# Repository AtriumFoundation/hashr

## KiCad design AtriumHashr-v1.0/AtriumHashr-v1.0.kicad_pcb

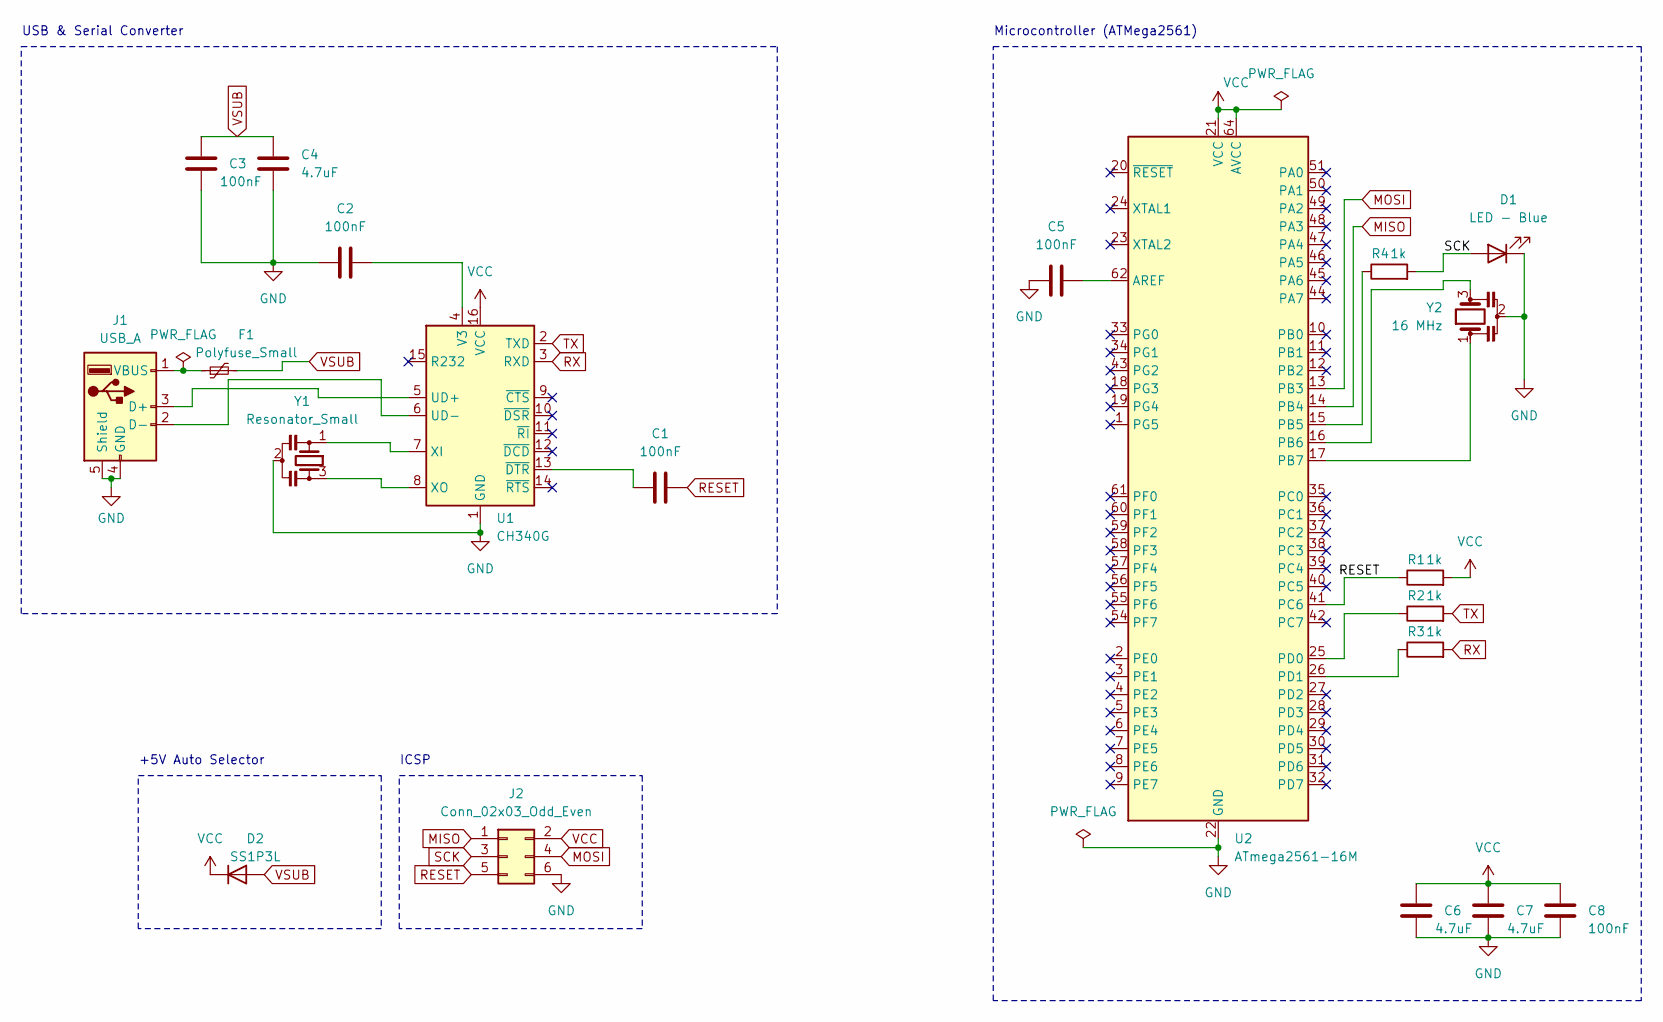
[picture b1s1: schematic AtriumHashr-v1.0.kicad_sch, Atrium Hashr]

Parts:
C1, C2, C3, C5, C8: 100nF; C_0402_1005Metric
C4, C6, C7: 4.7uF; C_0402_1005Metric
D1: LED - Blue; LED_0402_1005Metric
D2: SS1P3L; D_0402_1005Metric
F1: Polyfuse_Small; Fuse_0402_1005Metric
J1: USB_A; USB_A_CNCTech_1001-011-01101_Horizontal
J2: Conn_02x03_Odd_Even; PinHeader_2x03_P2.54mm_Vertical
R1, R2, R3, R4: 1k; R_0402_1005Metric
U1: CH340G; SOIC-16_3.9x9.9mm_P1.27mm
U2: ATmega2561-16M; QFN-64-1EP_9x9mm_P0.5mm_EP7.65x7.65mm
Y1: Resonator_Small; Resonator_SMD-3Pin_7.2x3.0mm
Y2: 16 MHz; Resonator_SMD-3Pin_7.2x3.0mm

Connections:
GND: C2.1, C3.1, C4.1, C5.1, C6.2, C7.2, C8.2, D1.1 (K), J1.4 (GND), J1.5 (Shield), J2.6, U1.1 (GND), U2.22 (GND), U2.53 (GND), U2.63 (GND), U2.65 (GND), Y1.2, Y2.2
MISO: J2.1, U2.14 (PB4)
MOSI: J2.4, U2.13 (PB3)
unnamed: J1.3 (D+), U1.5 (UD+)
unnamed: J1.2 (D-), U1.6 (UD-)
unnamed: F1.1, J1.1 (VBUS)
unnamed: C2.2, U1.4 (V3)
unnamed: U1.7 (XI), Y1.1
unnamed: U1.8 (XO), Y1.3
unnamed: C1.1, U1.13 (~DTR)
unnamed: C5.2, U2.62 (AREF)
unnamed: R4.1, U2.15 (PB5)
unnamed: U2.16 (PB6), Y2.3
unnamed: U2.17 (PB7), Y2.1
unnamed: R2.1, U2.25 (PD0)
unnamed: R3.1, U2.26 (PD1)
RESET: C1.2, J2.5, R1.1, U2.41 (PC6)
RX: R3.2, U1.3 (RXD)
SCK: D1.2 (A), J2.3, R4.2
TX: R2.2, U1.2 (TXD)
VCC: C6.1, C7.1, C8.1, D2.1 (K), J2.2, R1.2, U1.16 (VCC), U2.21 (VCC), U2.52 (VCC), U2.64 (AVCC)
VSUB: C3.2, C4.2, D2.2 (A), F1.2

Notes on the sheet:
USB & Serial Converter
Microcontroller (ATMega2561)
ICSP
+5V Auto Selector

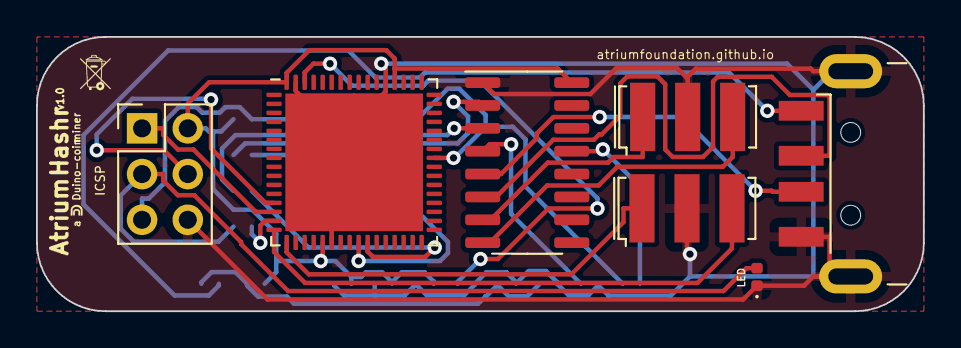
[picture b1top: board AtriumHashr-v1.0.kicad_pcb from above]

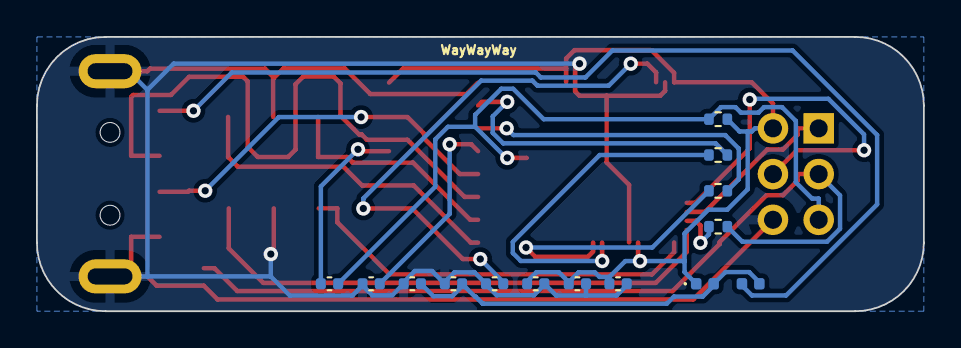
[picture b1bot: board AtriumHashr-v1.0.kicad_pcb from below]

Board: 2 copper layers, 49.3 x 15.2 mm, 21 parts (14 on the bottom side), 22 nets.

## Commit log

2024-01-04 v1.0 upload
